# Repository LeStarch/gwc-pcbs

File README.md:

# gwc-pcbs

How to set up:

1. Clone repository and submodules:

```
git clone --recurse-submodules https://github.com/LeStarch/gwc-pcbs
```

2. Install KiCad: https://www.kicad.org/download/

3. Open KiCad and Project

4. Add footprint library to kicad: https://docs.kicad.org/6.0/en/pcbnew/pcbnew_footprints_and_libraries.html

> [!Note]
> Footprint library is in cloned repo at kicad-footprints/personal.pretty

## Parts

| Part                    | Possible Choice | Notes |
|-------------------------|-----------------|-------|
| CR2032 Battery Holder   | [Amazon](https://www.amazon.com/gp/product/B06XF3K4NP) | |
| CR2032 Battery          | [Amazon](https://www.amazon.com/gp/product/B07LGJH4X7) | |
| 2x LEDs                 | [Amazon](https://www.amazon.com/gp/product/B01C19ENG4) | LEDs and resistor must pair: v3.2V LEDs / 0 ohm resistor |
| 2x SMD Resistors (0805) | [Amazon](https://www.amazon.com/gp/product/B00BXXJBSA) | LEDs and resistor must pair: v3.2V LEDs / 0 ohm resistor |
| Switch                  | [Amazon](https://www.amazon.com/gp/product/B007QAJUUS) | SPSD 1P2T 3 Pin 3mm 2.54mm pin pitch |

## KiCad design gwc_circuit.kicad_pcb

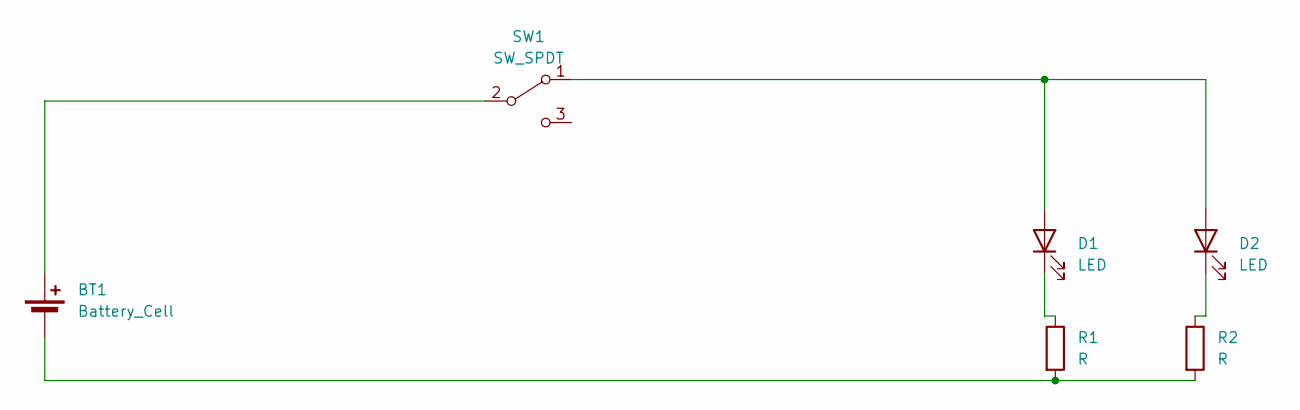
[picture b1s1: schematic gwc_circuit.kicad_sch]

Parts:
BT1: Battery_Cell; cr2032
D1, D2: LED; LED_D5.0mm
R1, R2: R; R_0805_2012Metric
SW1: SW_SPDT; PinSocket_1x03_P2.54mm_Vertical

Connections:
unnamed: BT1.1 (+), SW1.2 (B)
unnamed: BT1.2 (-), R1.2, R2.2
unnamed: D1.2 (A), D2.2 (A), SW1.1 (A)
unnamed: D1.1 (K), R1.1
unnamed: D2.1 (K), R2.1

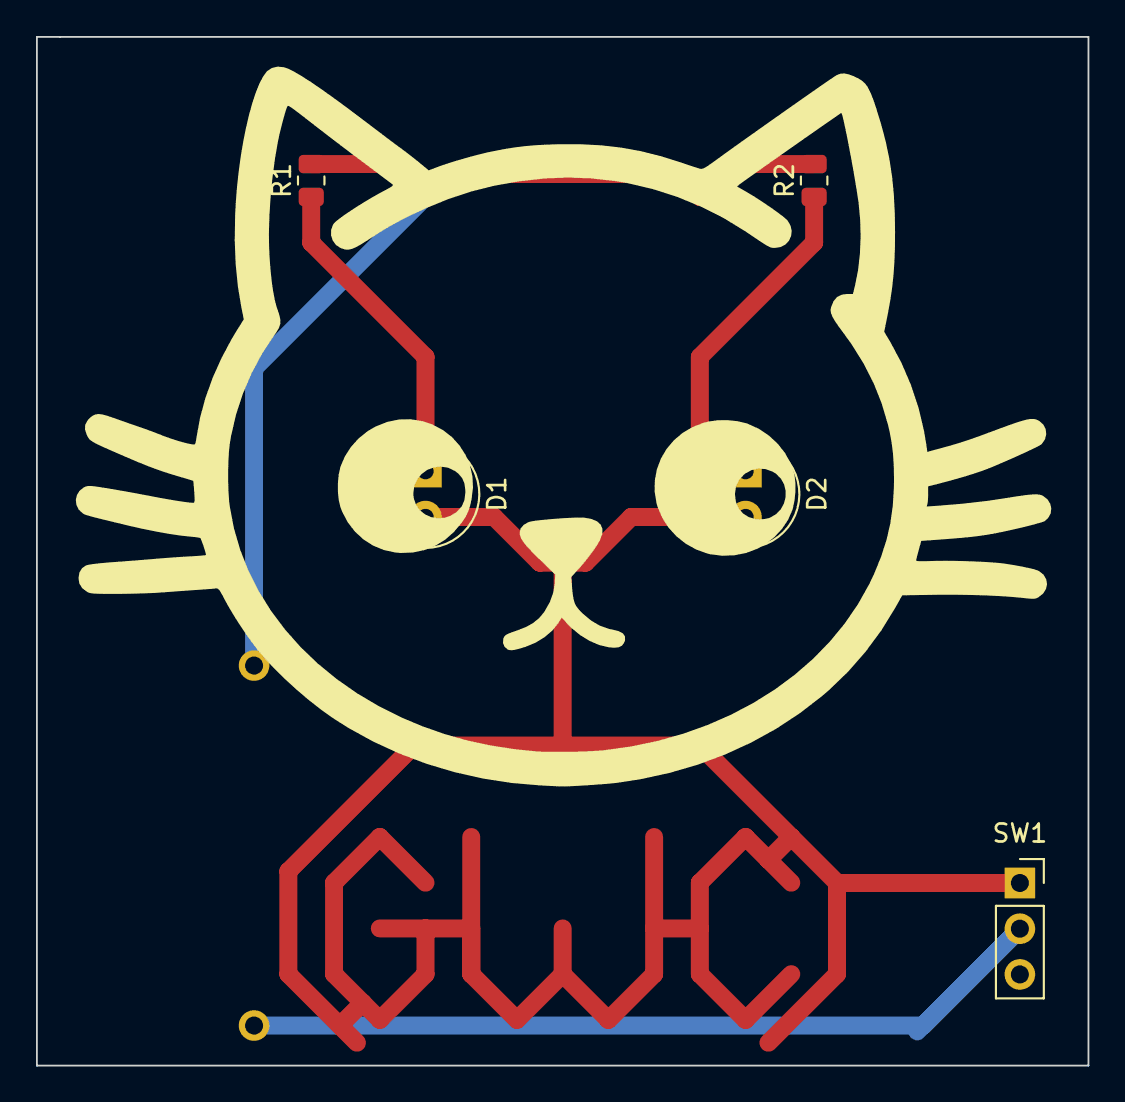
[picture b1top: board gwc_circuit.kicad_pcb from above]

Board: 2 copper layers, 58.4 x 57.1 mm, 6 parts (1 on the bottom side), 5 nets.

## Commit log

2024-09-15 GWC circuit 2023/2024
2024-09-15 Adding footprints as sub library
2024-09-15 Kicad 8.0 and instructions
2024-09-15 Adding parts list
